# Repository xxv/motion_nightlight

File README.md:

Motion detector night light
===========================

A light to illuminate your dark hallway on your way to the bathroom.

Ingredients
-----------

### Custom parts
* fully-populated and assembled PCB
* laser-cut wooden housing (`housing/housing_lasercut.scad`), cut from 3mm plywood
* laser-cut or 3D printed front grate (`housing/front_grate.svg`), 1.5mm black acrylic
* laser-cut diffuser holder (`housing/diffuser_holder.scad`), cut from 3mm black acrylic
* 3D printed board holder (`housing/board_holder.scad`)
* 3D printed battery plate (`housing/battery_plate.scad`)

### Vitamins
* 2x M2.5x8 black flat head bolt with washer and nut McMaster: 91294A016,
  90591A270, 93475a196
* 10x M2.2 6.5mm round head screws for sheet metal McMaster: 94997a125
* 3x AA batteries

### Other bits
* Diffuser (`housing/diffuser.scad`) cut from LEE Filters 810 Zircon Diffusion
  1 (or similar)
* Wood glue (+ [clamps](https://github.com/xxv/corner-clamp))
* Super glue
* 2mm-wide double-stick tape or similar

Main Assembly
-------------

1. Assemble PCB. Use M2.5x8 hardware to fasten battery holder to board.
2. Assemble diffuser assembly (see below).
3. Cut out main enclosure.
4. Glue main enclosure together with wood glue. Clamp and wipe off excess glue
   with a damp paper towel.
5. Glue battery plate to battery cover with super glue. (center carefully)
6. Once main enclosure glue is dry, screw board holder to it with M2.2 screws.
7. Screw board to board holder using M2.2 screws.
8. Slide the diffuser assembly into place. It should fit snugly, but not fall out.
9. Put fresh batteries into the night light. Don't put the battery cover on yet.
10. Calibrate the ambient light sensor.
    1. Bringing the night light into a dark room.
    2. Pull out the middle battery.
    3. Holding down both buttons, re-insert the middle battery.
    4. The status LED should blink three times to indicate that the calibration has been saved.

Diffuser Assembly
-----------------

1. Cut out the diffuser stand (4 identical parts) and assemble with super glue.
2. Cut out the diffuser from the Zircon 810 sheet using the diffuser template.
   This material is polyester and can be laser cut if desired.
3. Adhere the diffuser to the diffuser stand using the double-stick tape.
4. Cut out the diffuser decorative grate `front_grate.svg`. Note the
   non-commercial terms for this part in the license at the bottom.
5. Adhere the diffuser decorative grate to the diffuser using 2mm double-stick tape.

License
-------

* The PCB design and associated firmware are licensed under the GPLv3.
* The diffuser grate artwork (`front_grate.svg` and derivatives) is licensed under
  the Creative Commons CC-BY-NC-SA 4.0. If you wish to sell night lights using
  these files, you must use your own design for this one part. Consider this an
  opportunity to make your night light truly your own!
* All of the mechanical parts (housing, board stand, etc.) are available
  licensed under the Creative Commons CC-BY-SA 4.0 license.

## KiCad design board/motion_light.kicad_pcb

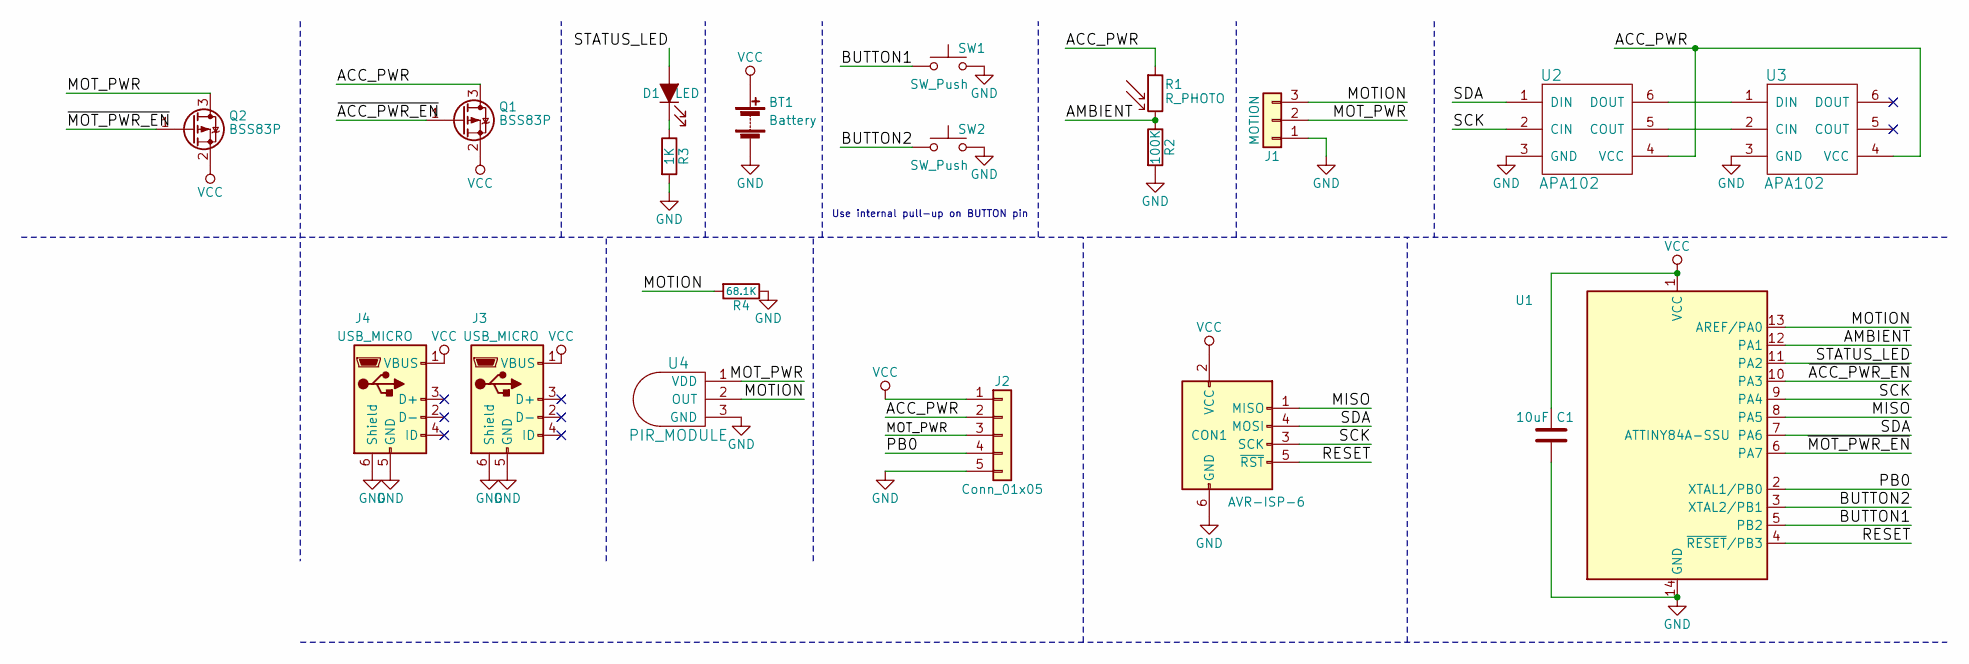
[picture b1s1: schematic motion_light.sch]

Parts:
BT1: Battery; Keystone_2464_3xAA; MPN 2464
C1: 10uF; C_0805_2012Metric_Pad1.15x1.40mm_HandSolder; MPN CL21A106KQCLRNC
CON1: AVR-ISP-6; PinHeader_2x03_P2.54mm_Vertical; MPN M20-9980345
D1: LED; LED_0805_2012Metric_Pad1.15x1.40mm_HandSolder
J1: MOTION; PinHeader_1x03_P2.54mm_Horizontal; MPN PRPC040SBAN-M71RC
J2: Conn_01x05; PinHeader_1x05_P2.54mm_Vertical
J3, J4: USB_MICRO; USB_Micro-B_Molex-105017-0001
Q1, Q2: BSS83P; SOT-23; MPN BSS83PH6327XTSA1
R1: R_PHOTO; R_LDR_5.1x4.3mm_P3.4mm_Vertical; MPN PDV-P8103
R2: 100K; R_0805_2012Metric_Pad1.15x1.40mm_HandSolder; MPN RNCP0805FTD10K0
R3: 1K; R_0805_2012Metric_Pad1.15x1.40mm_HandSolder; MPN RNCP0805FTD1K00
R4: 68.1K; R_0805_2012Metric_Pad1.15x1.40mm_HandSolder; MPN RNCP0805FTD68K1
SW1, SW2: SW_Push; SW_Tactile_SPST_Angled_PTS645Vx83-2LFS; MPN PTS645VL83-2 LFS
U1: ATTINY84A-SSU; SOIC-14_3.9x8.7mm_P1.27mm; MPN ATTINY84A-SSUR
U2, U3: APA102; APA102_hand_solder; MPN SK9822
U4: PIR_MODULE; PaPIR_PIR_SENSOR; MPN EKMC1604112

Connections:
/ACC_PWR: J2.2, Q1.3 (D), R1.1, U2.4 (VCC), U3.4 (VCC)
/AMBIENT: R1.2, R2.1, U1.12 (PA1)
/BUTTON1: SW1.1, U1.5 (PB2)
/BUTTON2: SW2.1, U1.3 (XTAL2/PB1)
/MISO: CON1.1 (MISO), U1.8 (PA5)
/MOTION: J1.3, R4.2, U1.13 (AREF/PA0), U4.2 (OUT)
/MOT_PWR: J1.2, J2.3, Q2.3 (D), U4.1 (VDD)
/PB0: J2.4, U1.2 (XTAL1/PB0)
/RESET: CON1.5 (~RST), U1.4 (~RESET~/PB3)
/SCK: CON1.3 (SCK), U1.9 (PA4), U2.2 (CIN)
/SDA: CON1.4 (MOSI), U1.7 (PA6), U2.1 (DIN)
/STATUS_LED: D1.2 (A), U1.11 (PA2)
/~ACC_PWR_EN: Q1.1 (G), U1.10 (PA3)
/~MOT_PWR_EN: Q2.1 (G), U1.6 (PA7)
GND: BT1.2 (-), C1.2, CON1.6 (GND), J1.1, J2.5, J3.5 (GND), J3.6 (Shield), J4.5 (GND), J4.6 (Shield), R2.2, R3.2, R4.1, SW1.2, SW2.2, U1.14 (GND), U2.3 (GND), U3.3 (GND), U4.3 (GND)
unnamed: D1.1 (K), R3.1
unnamed: U2.5 (COUT), U3.2 (CIN)
unnamed: U2.6 (DOUT), U3.1 (DIN)
VCC: BT1.1 (+), C1.1, CON1.2 (VCC), J2.1, J3.1 (VBUS), J4.1 (VBUS), Q1.2 (S), Q2.2 (S), U1.1 (VCC)

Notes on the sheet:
Use internal pull-up on BUTTON pin

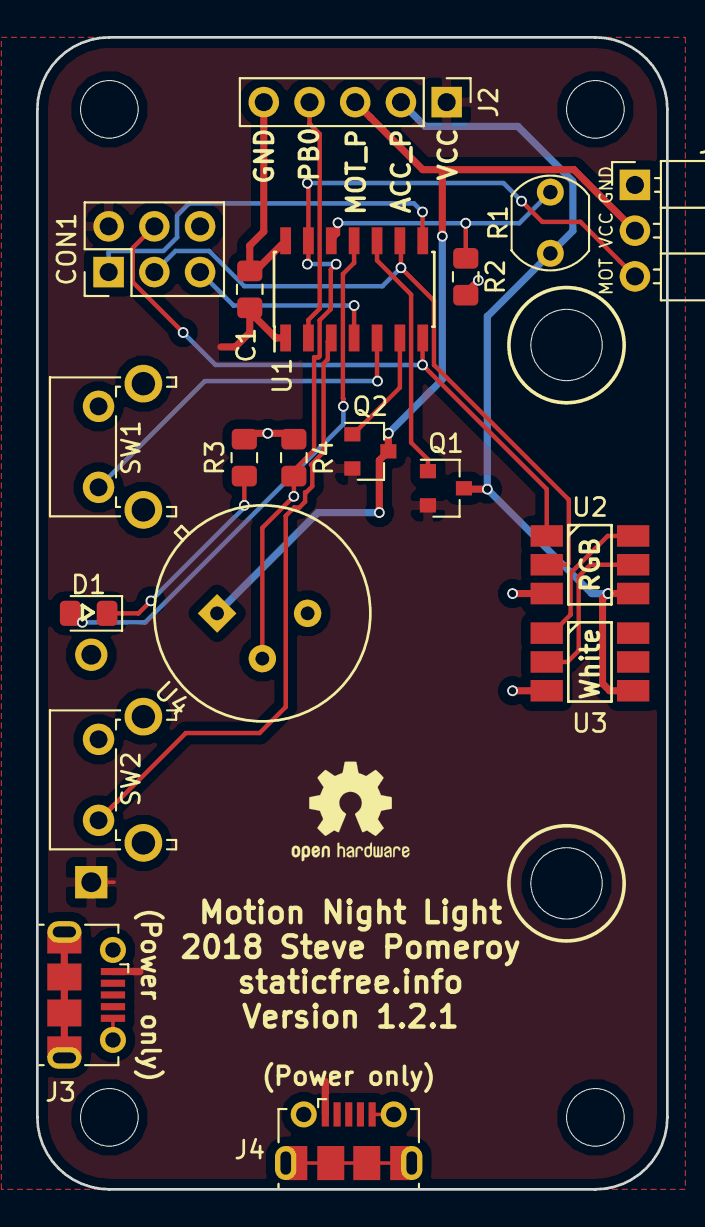
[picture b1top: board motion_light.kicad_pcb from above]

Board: 2 copper layers, 35.0 x 64.0 mm, 20 parts (1 on the bottom side), 19 nets.

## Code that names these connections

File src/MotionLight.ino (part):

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  { 0x000000, COLOR_MODE_RANDOM }, // show a random color, incl. white
};

const static int PIN_MOTION      = PIN_A0;
const static int PIN_AMBIENT     = A1;
const static int PIN_STATUS_LED  = PIN_A2;
const static int PIN_ACC_PWR_DIS = PIN_A3;
const static int PIN_MOT_PWR_DIS = PIN_A7;
const static int PIN_BUTTON_1    = PIN_B2;
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uint8_t palette_idx = 0;

/**
 * sleeping = low power, wake via motion
 * deep_sleeping = lowest power, wake via being dark
 * running = light is fading on/off/steady on
 */
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
APA102Controller_WithBrightness<PIN_SDA, PIN_SCK, BGR>ledController;

Button button1(PIN_BUTTON_1);
Button button2(PIN_BUTTON_2);

ISR (PCINT0_vect) {
  // Don't need to do anything, just wake up.
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  WDTCSR = 0x00; // disable watchdog

  if (DEBUG_WATCHDOG) {
    digitalWrite(PIN_STATUS_LED, HIGH);
  }

  woke_from_watchdog = true;
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
void watchdog_enable() {
  if (DEBUG_WATCHDOG) {
    digitalWrite(PIN_STATUS_LED, LOW);
  }

  bitSet(WDTCSR, WDIE);           // watchdog triggers an interrupt
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  digitalWrite(PIN_ACC_PWR_DIS, !is_powered);

  if (DEBUG_ACCESSORY_POWER) {
    digitalWrite(PIN_STATUS_LED, is_powered);
  }
}

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  if (deep_sleep) {
    deep_sleep_countdown = 0;
  } else {
    pciSetup(PIN_MOTION);
  }

  pciSetup(PIN_BUTTON_1);
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  sleep_enable();

  if (DEBUG_SLEEPING) {
    digitalWrite(PIN_STATUS_LED, LOW);
  }

  bitClear(ADCSRA, ADEN); // disable ADC
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  bitSet(ADCSRA, ADEN); // re-enable ADC

  if (DEBUG_SLEEPING) {
    digitalWrite(PIN_STATUS_LED, HIGH);
  }

  disable_pc_interrupts();
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}

void disable_pc_interrupts() {
  disable_pc_interrupts(PIN_MOTION);
  disable_pc_interrupts(PIN_BUTTON_1);
  disable_pc_interrupts(PIN_BUTTON_2);
}
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}

void led_test() {
  digitalWrite(PIN_STATUS_LED, HIGH);
  leds[WHITE_LED] = CRGB(0, 0, 0);
  leds[RGB_LED] = CRGB(20, 0, 0);
  FastLED.show();
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  leds[RGB_LED] = CRGB(0, 0, 0);
  leds[WHITE_LED] = CRGB(0, 0, 0);
  FastLED.show();
  digitalWrite(PIN_STATUS_LED, LOW);
}

int analogReadAverage(uint8_t pin, uint8_t count) {
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void setup() {
  button1.begin();
  button2.begin();
  pinMode(PIN_MOTION, INPUT);
  pinMode(PIN_AMBIENT, INPUT);
  pinMode(PIN_STATUS_LED, OUTPUT);
  pinMode(PIN_ACC_PWR_DIS, OUTPUT);
  pinMode(PIN_MOT_PWR_DIS, OUTPUT);
  FastLED.addLeds((CLEDController*) &ledController, leds, NUM_LEDS);
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  if (button1.isPressed() && button2.isPressed()) {
    // a delay to ensure there is no light from the white LED
    delay(100);
    ambient_darkness_level = analogReadAverage(PIN_AMBIENT, 10);
    save_settings();

    digitalWrite(PIN_STATUS_LED, LOW);
    delay(250);
    digitalWrite(PIN_STATUS_LED, HIGH);
    delay(250);
    digitalWrite(PIN_STATUS_LED, LOW);
    delay(250);
    digitalWrite(PIN_STATUS_LED, HIGH);
    delay(250);
    digitalWrite(PIN_STATUS_LED, LOW);
    delay(250);
    digitalWrite(PIN_STATUS_LED, HIGH);
    delay(250);
  }

  digitalWrite(PIN_STATUS_LED, LOW);
}

void handleSettingMode() {
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
void update_ambient_level() {
  if (is_dark_enough) {
    is_dark_enough = analogRead(PIN_AMBIENT) <=
                     (ambient_darkness_level + AMBIENT_HYSTERESIS);
  } else {
    is_dark_enough = analogRead(PIN_AMBIENT) <=
                     (ambient_darkness_level - AMBIENT_HYSTERESIS);
  }
}
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        // fall through
      case running:
        if (mode == setting) {
          digitalWrite(PIN_STATUS_LED, LOW);
        }
        set_motion_powered(true);
        break;
      case setting:
        digitalWrite(PIN_STATUS_LED, HIGH);
        break;
    }
    mode = newMode;
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    button2.read();

    set_accessory_powered(true);
    motion = digitalRead(PIN_MOTION);
    update_ambient_level();

    switch (mode) {
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  }

  if (DEBUG_AMBIENT) {
    digitalWrite(PIN_STATUS_LED, is_dark_enough);
  }

  if (DEBUG_MOTION) {
    digitalWrite(PIN_STATUS_LED, motion);
  }

  EVERY_N_MILLIS(2) {
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
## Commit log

2016-03-09 First working version
    Too bright though
2016-03-09 Add a hack in to set brightness using APA102 global brightness
    This seems the only way to get the LED dim enough
2016-03-09 Add README
2016-03-11 Add housing
    This revision has not been printed as of this commit, so tolerances may
    need to be tweaked.
2016-03-11 Add stls to ignore
2017-09-10 Only change brightness when needed
2017-09-10 Update gitignore
2017-09-19 First pass at basic motion + LEDs
2017-10-18 Add first pass at board
2017-10-30 Schematic revisions
    * Add BoM details
    * Add pull-down resistor on motion detector module
    * Change GPIO header to 1x5
2017-11-12 Add real parts to housing design
2017-11-12 Rework board; add mesh design
    * Make board an even size
    * Adjust position of motion detector
    * Improve model of PIR sensor
2017-11-21 Move ambient light sensor; center buttons and status LED
    * Improve silk documentation
2017-11-21 Add more silk docs
2017-11-26 Use boxmaker library to generate enclosure
2017-11-26 Tidy up photo resistor mockup
2017-11-26 Add screw slots
2017-11-26 Correct parts in BoM
2017-11-26 Add board mounting bracket
2017-11-26 Add wood screw model
2017-11-26 Add pretty rounded corners to mounting plate; tidy defs
2017-11-27 Redesign diffuser to be mounted on a stand-off
2017-11-27 Tweak screw holes
2017-11-27 Update keystone PN2464
2017-12-02 Add wings to firefly design
2017-12-04 Thin and simplify wings in design
2017-12-06 Fix PIR sensor footprint
2017-12-06 Update pins for new board
2017-12-06 Remove random color
2017-12-06 Fix PIR orientation; update PIR silk; add more silk labels
2017-12-09 Add basic button support
2017-12-16 Update PlatformIO
2017-12-17 Add running mode; add more color palettes
2017-12-17 Use all three elements in white LED
2017-12-17 Fix power-off bug
2017-12-17 Better handle button presses in sleep mode
2017-12-17 Add ambient light sensor support
2017-12-17 Clean up debug code
2017-12-28 Add decoupling cap
2017-12-28 Rotate LEDs to make them closer together and easier to solder
2018-01-06 Add basic power management
2018-03-02 Schematic changes of unknown variety
2018-03-02 Moar schematic changes
2018-03-02 Wall thickness to 3.3mm
2018-03-03 Make it easier to switch between 2d/3d in design
2018-03-03 Add battery plate holder
2018-03-03 Offset bottom parts for easier cutting
2018-08-02 Switch to KiCAD 5; add USB plugs
    * Update footprints and library symbols to KiCAD 5
    * Add optional USB plugs to power directly
2018-08-14 Fix broken pin mappings; add accessory powerdown
2018-08-14 Add watchdog timer
2018-08-14 Use global brightness for global dimming
    Because the SK9822s have non-terrible global brightness control, this
    can now be used for its intended function. If using APA102s, this should
    be reverted.
2018-08-14 Rename watchdog method
2018-08-15 Add hysteresis function to ambient light sensor
2018-08-19 Add deep sleep function
2018-08-19 Add loading/saving of settings to EEPROM
2018-08-19 Fiddly board updates
2018-08-20 Update mesh design
2018-08-20 Add separate power control for motion detector power
2018-08-20 Shutdown ADC to save power
2018-09-11 Add support for motion detector power down
2018-09-11 Switch to updated button library
2018-09-11 Allow on-board calibration of darkness sensor
2018-10-27 Increase screw overlap to improve print quality.
2018-10-27 Make more properly parametric
2018-11-23 Rotate motion detector to work with wall-oriented detector
2018-11-25 Update board BoM; upgrade symbols
2018-12-02 Tune battery cover
2018-12-03 Redo diffuser stand as lasercut part
2018-12-23 Laser cut diffuser stand doesn't need an offset
2018-12-23 Refine battery panel.
2018-12-23 Add small angle to battery panel to ease opening
2019-01-01 Add a little extra z-height to the buttons
2019-01-05 Move various housing parts to separate files for rendering
2019-01-05 Use 100K resistor for better ambient light sensitivity
2019-01-05 Increase perimeter thickness on design
2019-01-05 It's not made of metal
2019-01-26 Improve ambient brightness calibration
2019-01-26 Break parts into separate .scad files
2019-01-26 Cleanup gitignore
2019-01-26 Rewrite README
2019-01-26 Add vertical stand
2019-01-26 Add corner taper to help prevent plywood delamination
2019-01-26 Add GPLv3 license
2019-01-26 Tidy gitignores
2019-01-26 Add copy of boxmaker
2019-01-26 Add housing badge
2019-02-16 Update with new resistor value
2019-03-10 Make the screw pilot holes smaller
2019-03-10 Make the button holes bigger
2019-03-25 Add random color demo mode
2019-03-26 Increase animation speed to make it seem more deliberate
2019-03-26 Remove stray global
2019-03-26 Remove preprocessor macros
2019-03-26 Cleanups
2019-03-26 Improve brightness setting when in random mode
2019-04-20 Redo the labeling
2019-12-08 Clean up small mesh error
2019-12-08 Fix small mesh error that prevented printing
2019-12-08 Add mockup
2019-12-11 Add pio to ignore
2019-12-21 Tighten up inset for battery door new prints
2019-12-29 Add manual
2019-12-29 Add link to clamps
2020-05-01 Fix typo in the manual
